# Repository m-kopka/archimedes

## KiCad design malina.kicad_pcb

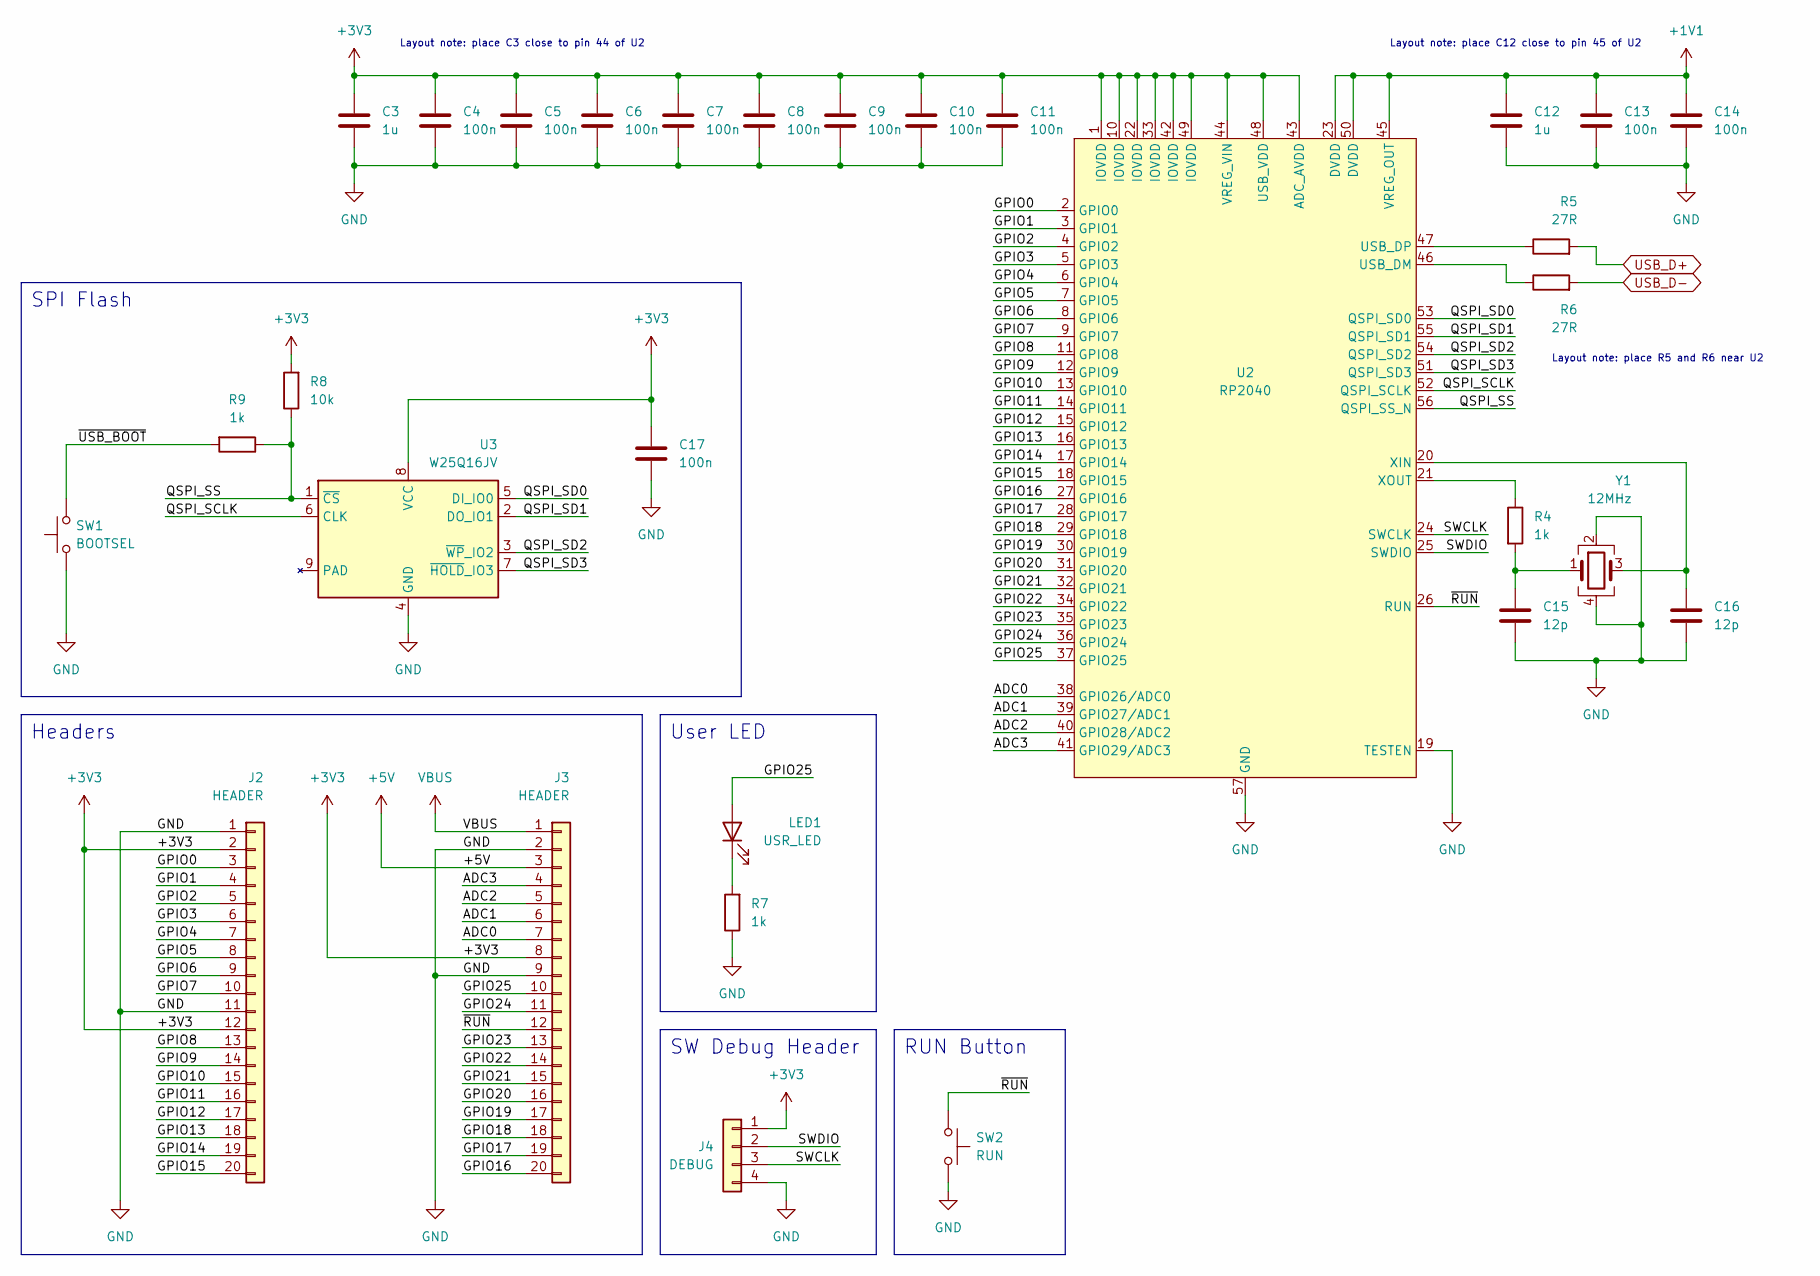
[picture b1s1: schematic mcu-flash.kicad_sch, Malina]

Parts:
C3, C12: 1u; C_0402_1005Metric
C4, C5, C6, C7, C8, C9, C10, C11, C13, C14, C17: 100n; C_0402_1005Metric
C15, C16: 12p; C_0402_1005Metric
J2, J3: HEADER; PinHeader_1x20_P2.54mm_Vertical
J4: DEBUG; PinHeader_1x04_P2.54mm_Horizontal
LED1: USR_LED; LED 0603
R4, R7, R9: 1k; R_0402_1005Metric
R5, R6: 27R; R_0402_1005Metric
R8: 10k; R_0402_1005Metric
SW1: BOOTSEL; Tactile Switch 4.2x3.2mm
SW2: RUN; Tactile Switch 4.2x3.2mm
U2: RP2040; QFN-56 7x7mm P0.4mm
U3: W25Q16JV; USON-8 2x3mm
Y1: 12MHz; Crystal 3225 3.2x2.5mm 4pin

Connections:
+1V1: C12.1, C13.1, C14.1, U2.23 (DVDD), U2.45 (VREG_OUT), U2.50 (DVDD)
+3V3: C3.1, C4.1, C5.1, C6.1, C7.1, C8.1, C9.1, C10.1, C11.1, C17.1, J2.2, J2.12, J3.8, J4.1, R8.2, U2.1 (IOVDD), U2.10 (IOVDD), U2.22 (IOVDD), U2.33 (IOVDD), U2.42 (IOVDD), U2.43 (ADC_AVDD), U2.44 (VREG_VIN), U2.48 (USB_VDD), U2.49 (IOVDD), U3.8 (VCC); also elsewhere on the board
+5V: J3.3; also elsewhere on the board
/MCU and Flash/ADC0: J3.7, U2.38 (GPIO26/ADC0)
/MCU and Flash/ADC1: J3.6, U2.39 (GPIO27/ADC1)
/MCU and Flash/ADC2: J3.5, U2.40 (GPIO28/ADC2)
/MCU and Flash/ADC3: J3.4, U2.41 (GPIO29/ADC3)
/MCU and Flash/GPIO0: J2.3, U2.2 (GPIO0)
/MCU and Flash/GPIO1: J2.4, U2.3 (GPIO1)
/MCU and Flash/GPIO2: J2.5, U2.4 (GPIO2)
/MCU and Flash/GPIO3: J2.6, U2.5 (GPIO3)
/MCU and Flash/GPIO4: J2.7, U2.6 (GPIO4)
/MCU and Flash/GPIO5: J2.8, U2.7 (GPIO5)
/MCU and Flash/GPIO6: J2.9, U2.8 (GPIO6)
/MCU and Flash/GPIO7: J2.10, U2.9 (GPIO7)
/MCU and Flash/GPIO8: J2.13, U2.11 (GPIO8)
/MCU and Flash/GPIO9: J2.14, U2.12 (GPIO9)
/MCU and Flash/GPIO10: J2.15, U2.13 (GPIO10)
/MCU and Flash/GPIO11: J2.16, U2.14 (GPIO11)
/MCU and Flash/GPIO12: J2.17, U2.15 (GPIO12)
/MCU and Flash/GPIO13: J2.18, U2.16 (GPIO13)
/MCU and Flash/GPIO14: J2.19, U2.17 (GPIO14)
/MCU and Flash/GPIO15: J2.20, U2.18 (GPIO15)
/MCU and Flash/GPIO16: J3.20, U2.27 (GPIO16)
/MCU and Flash/GPIO17: J3.19, U2.28 (GPIO17)
/MCU and Flash/GPIO18: J3.18, U2.29 (GPIO18)
/MCU and Flash/GPIO19: J3.17, U2.30 (GPIO19)
/MCU and Flash/GPIO20: J3.16, U2.31 (GPIO20)
/MCU and Flash/GPIO21: J3.15, U2.32 (GPIO21)
/MCU and Flash/GPIO22: J3.14, U2.34 (GPIO22)
/MCU and Flash/GPIO23: J3.13, U2.35 (GPIO23)
/MCU and Flash/GPIO24: J3.11, U2.36 (GPIO24)
/MCU and Flash/GPIO25: J3.10, LED1.2 (A), U2.37 (GPIO25)
/MCU and Flash/QSPI_SCLK: U2.52 (QSPI_SCLK), U3.6 (CLK)
/MCU and Flash/QSPI_SD0: U2.53 (QSPI_SD0), U3.5 (DI_IO0)
/MCU and Flash/QSPI_SD1: U2.55 (QSPI_SD1), U3.2 (DO_IO1)
/MCU and Flash/QSPI_SD2: U2.54 (QSPI_SD2), U3.3 (~WP_IO2)
/MCU and Flash/QSPI_SD3: U2.51 (QSPI_SD3), U3.7 (~HOLD_IO3)
/MCU and Flash/QSPI_SS: R8.1, R9.1, U2.56 (QSPI_SS_N), U3.1 (~CS)
/MCU and Flash/SWCLK: J4.3, U2.24 (SWCLK)
/MCU and Flash/SWDIO: J4.2, U2.25 (SWDIO)
/MCU and Flash/~RUN: J3.12, SW2.1, U2.26 (RUN)
/MCU and Flash/~USB_BOOT: R9.2, SW1.1
GND: C3.2, C4.2, C5.2, C6.2, C7.2, C8.2, C9.2, C10.2, C11.2, C12.2, C13.2, C14.2, C15.2, C16.2, C17.2, J2.1, J2.11, J3.2, J3.9, J4.4, R7.1, SW1.2, SW2.2, U2.19 (TESTEN), U2.57 (GND), U3.4 (GND), Y1.2, Y1.4; also elsewhere on the board
unnamed: C15.1, R4.2, Y1.1
unnamed: C16.1, U2.20 (XIN), Y1.3
unnamed: LED1.1 (K), R7.2
unnamed: R4.1, U2.21 (XOUT)
unnamed: R5.1, U2.47 (USB_DP)
unnamed: R6.1, U2.46 (USB_DM)
USB_D+: R5.2; also elsewhere on the board
USB_D-: R6.2; also elsewhere on the board
VBUS: J3.1; also elsewhere on the board

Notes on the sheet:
Layout note: place C3 close to pin 44 of U2
Headers
SW Debug Header
Layout note: place R5 and R6 near U2
RUN Button
User LED
SPI Flash
Layout note: place C12 close to pin 45 of U2

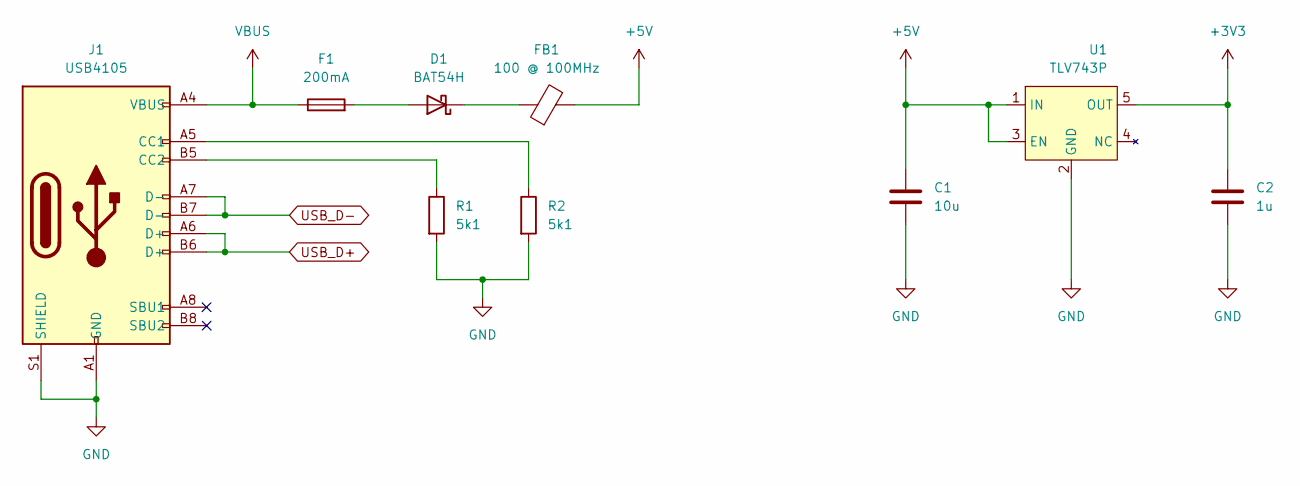
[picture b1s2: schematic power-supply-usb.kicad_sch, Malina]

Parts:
C1: 10u; C_0603_1608Metric
C2: 1u; C_0402_1005Metric
D1: BAT54H; SOD-123LF
F1: 200mA; R_0603_1608Metric
FB1: 100 @ 100MHz; R_0402_1005Metric
J1: USB4105
R1, R2: 5k1; R_0402_1005Metric
U1: TLV743P; SOT-23-5L

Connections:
+3V3: C2.1, U1.5 (OUT); also elsewhere on the board
+5V: C1.1, FB1.2, U1.1 (IN), U1.3 (EN); also elsewhere on the board
GND: C1.2, C2.2, J1.A1 (GND), J1.A12 (GND), J1.B1 (GND), J1.B12 (GND), J1.S1 (SHIELD), R1.2, R2.2, U1.2 (GND); also elsewhere on the board
unnamed: D1.1 (K), FB1.1
unnamed: D1.2 (A), F1.2
unnamed: J1.A5 (CC1), R2.1
unnamed: J1.B5 (CC2), R1.1
USB_D+: J1.A6 (D+), J1.B6 (D+); also elsewhere on the board
USB_D-: J1.A7 (D-), J1.B7 (D-); also elsewhere on the board
VBUS: F1.1, J1.A4 (VBUS), J1.A9 (VBUS), J1.B4 (VBUS), J1.B9 (VBUS); also elsewhere on the board

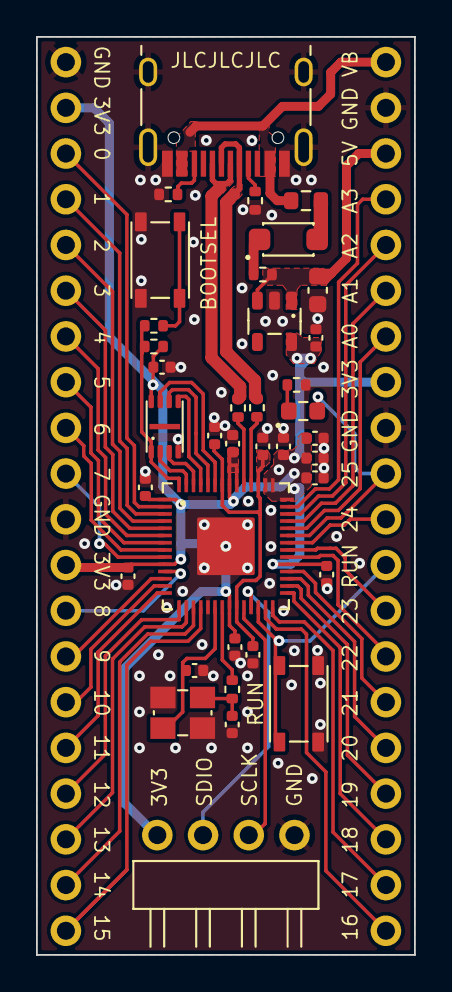
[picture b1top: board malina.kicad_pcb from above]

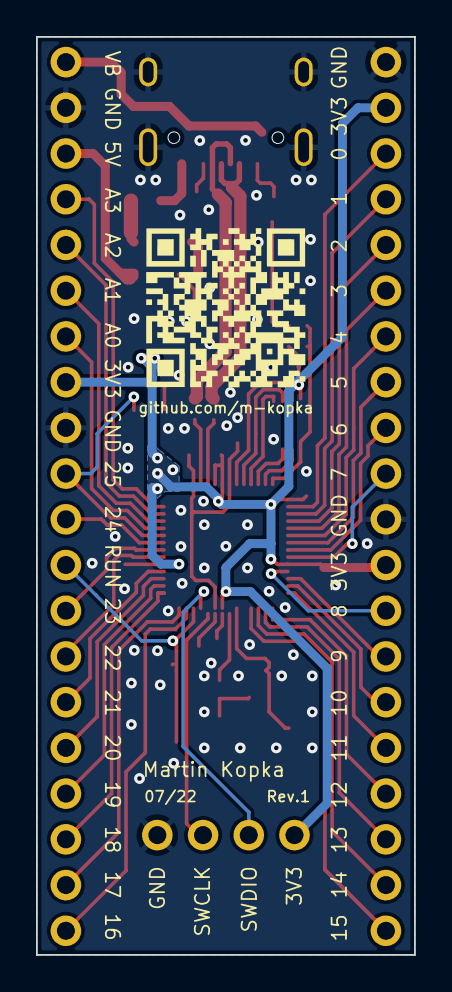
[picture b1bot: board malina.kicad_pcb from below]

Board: 2 copper layers, 21.0 x 51.0 mm, 39 parts (2 on the bottom side), 57 nets.

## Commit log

2024-03-02 add: README.md
2024-03-02 add: pdf schematics
